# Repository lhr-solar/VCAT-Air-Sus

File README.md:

# Air-Suspension Boards

> **Project:** Longhorn Racing Solar - Hardware & Telemetry
> **Author:** Karthik Kurapati 

This repository contains the hardware design files for 4 sensors on the car: Suspension (Linear Potentiometers), Pitot, Temperature/Pressure, and RideHeight. 

## Table of Contents
1. [Telemetry CAN Overview](#CAN-overview)
2. [PSOM Boards](#psom-boards)
    - [Pitot Board](#1-pitot-board)
    - [Sus-RH (Suspension & Ride Height) Board](#2-sus-rh-board)
3. [Breakout Boards](#breakout-boards)
    - [Temperature Breakout](#3-temperature-breakout)
    - [Ride Height Breakout](#4-ride-height-breakout)

---

## Telemetry CAN Overview

P - Pitot Board
T - Temperature Breakout
L - Telemetry Leader
S - Sus-RH Board
RH - Sus-RH Board + Ride Height Breakout
W - Wheels Board

---

## PSOM Boards

These boards integrate a PSOM to collect data from sensors 

### 1. Pitot Board
**Function:** Measures the vehicle's true airspeed via a pitot sensor. Relays data sent by the temperature sensor to telemetry leader. 
**Sensors**: HSCDRRN010NDSA3

### 2. Sus-RH Board
**Function:** Measures linear potentiometer (suspension) travel on the car via ADC. Interfaces with ride height breakout. 
**Sensor:** LPPS-12

---

## Breakout Boards

Simple boards that use nano-fits to connect to the boards above to add functionality. Both breakouts use I2C to communicate over the distance. 

### 3. Temperature Breakout
**Function:** Provide valuable temperature, pressure, humidity, and air density information to improve estimate of airspeed. 
**Sensor:** BME280 

### 4. Ride Height Breakout (IR Board)
**Function:** Provides the distance from the bottom of the car to the road in multiple areas.
**Sensor** VL53L0X

---

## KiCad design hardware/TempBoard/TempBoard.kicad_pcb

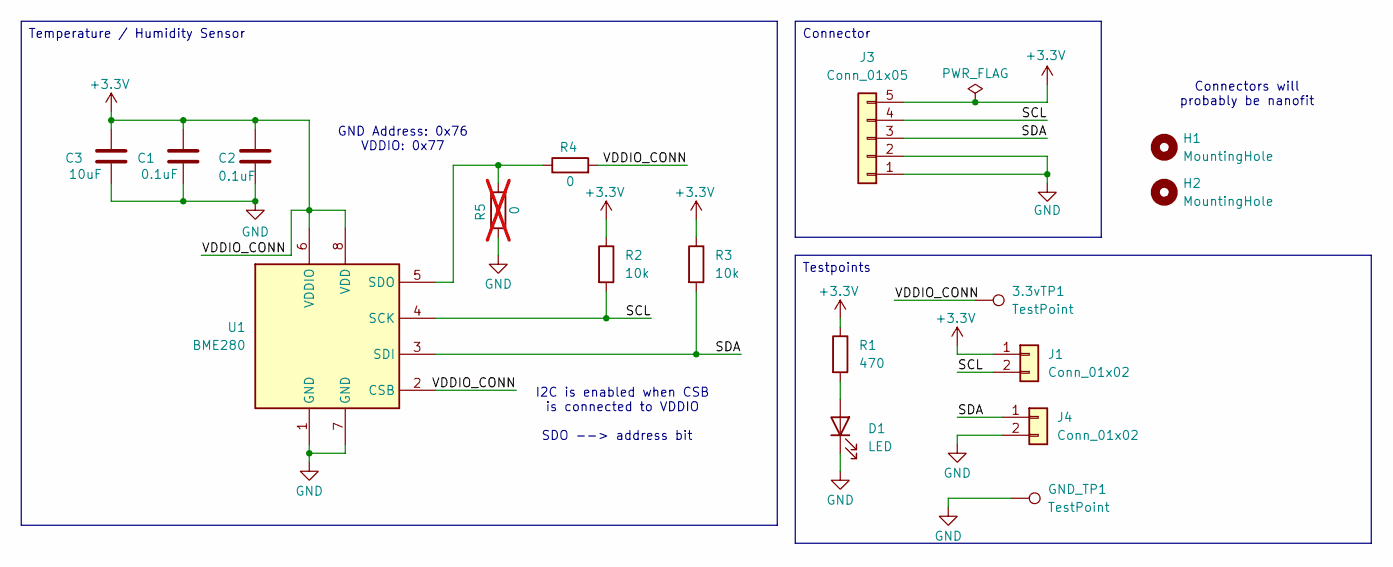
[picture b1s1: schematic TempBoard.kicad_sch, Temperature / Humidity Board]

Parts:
3.3vTP1: TestPoint; TestPoint_THTPad_1.0x1.0mm_Drill0.5mm
C1, C2: 0.1uF; C_0603_1608Metric_Pad1.08x0.95mm_HandSolder
C3: 10uF; C_0805_2012Metric_Pad1.18x1.45mm_HandSolder
D1: LED; LED_0603_1608Metric_Pad1.05x0.95mm_HandSolder
GND_TP1: TestPoint; TestPoint_THTPad_1.0x1.0mm_Drill0.5mm
H1, H2: MountingHole; MountingHole_3.2mm_M3
J1, J4: Conn_01x02; PinHeader_1x02_P2.54mm_Vertical
J3: Conn_01x05; Molex_Nano-Fit_105313-xx05_1x05_P2.50mm_Horizontal
R1: 470; R_0603_1608Metric_Pad0.98x0.95mm_HandSolder
R2, R3: 10k; R_0603_1608Metric_Pad0.98x0.95mm_HandSolder
R4: 0; R_0603_1608Metric_Pad0.98x0.95mm_HandSolder
R5: 0; R_0603_1608Metric_Pad0.98x0.95mm_HandSolder; not fitted
U1: BME280; Bosch_LGA-8_2.5x2.5mm_P0.65mm_ClockwisePinNumbering

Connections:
+3.3V: 3.3vTP1.1, C1.1, C2.1, C3.1, J1.1, J3.5, R1.1, R2.1, R3.1, R4.2, U1.2 (CSB), U1.6 (VDDIO), U1.8 (VDD)
/SCL: J1.2, J3.4, R2.2, U1.4 (SCK)
/SDA: J3.3, J4.1, R3.2, U1.3 (SDI)
GND: C1.2, C2.2, C3.2, D1.1 (K), GND_TP1.1, J3.1, J3.2, J4.2, R5.1, U1.1 (GND), U1.7 (GND)
unnamed: D1.2 (A), R1.2
unnamed: R4.1, R5.2, U1.5 (SDO)

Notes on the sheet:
Connectors will probably be nanofit
I2C is enabled when CSB is connected to VDDIO
GND Address: 0x76 VDDIO: 0x77
SDO --> address bit
Connector
Testpoints
Temperature / Humidity Sensor

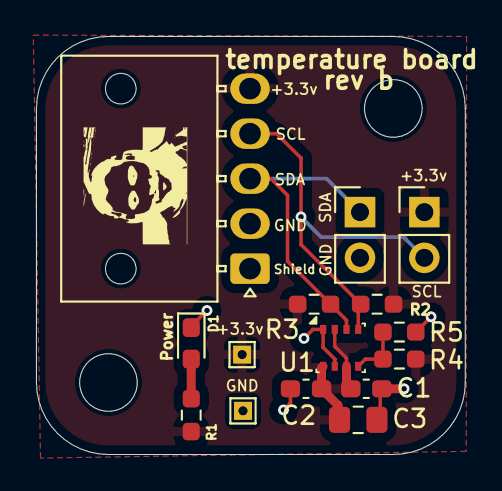
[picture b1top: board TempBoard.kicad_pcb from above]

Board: 2 copper layers, 23.8 x 23.2 mm, 17 parts (0 on the bottom side), 6 nets.

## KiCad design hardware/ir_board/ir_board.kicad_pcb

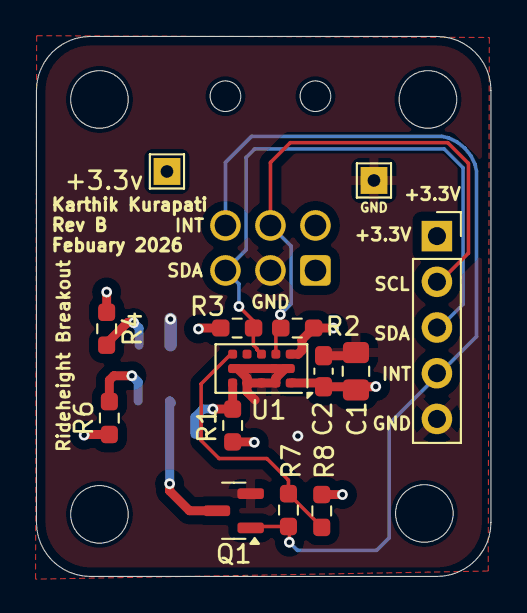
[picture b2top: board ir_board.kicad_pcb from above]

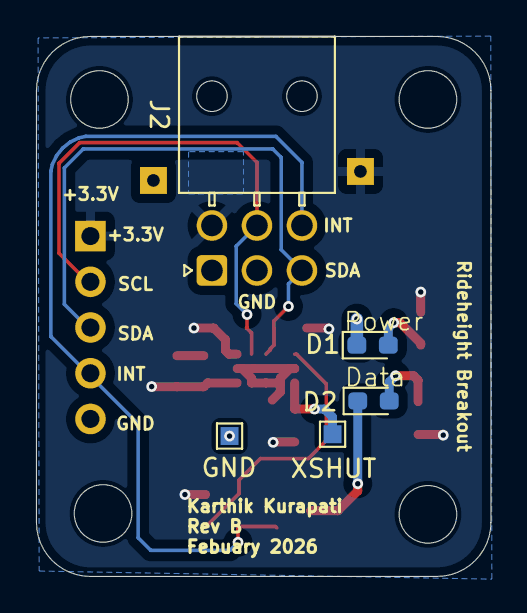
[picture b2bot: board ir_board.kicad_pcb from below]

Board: 2 copper layers, 25.2 x 30.0 mm, 23 parts (5 on the bottom side), 10 nets.

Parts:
+3.3v: TestPoint; TestPoint_THTPad_1.5x1.5mm_Drill0.7mm
C1: 4.7uf; C_0805_2012Metric_Pad1.18x1.45mm_HandSolder
C2: 0.1uf; C_0603_1608Metric_Pad1.08x0.95mm_HandSolder
D1, D2: LED; LED_0603_1608Metric_Pad1.05x0.95mm_HandSolder
GND: TestPoint; TestPoint_THTPad_1.5x1.5mm_Drill0.7mm
GND#2: TestPoint; TestPoint_Pad_1.0x1.0mm
H1, H2, H3, H4: MountingHole; MountingHole_3.2mm_M3
J1: Conn_01x05; PinSocket_1x05_P2.54mm_Vertical
J2: Conn_01x06; Molex_Nano-Fit_105314-xx06_2x03_P2.50mm_Horizontal
Q1: IRLML0030; SOT-23
R1: 10k; R_0603_1608Metric_Pad0.98x0.95mm_HandSolder
R2, R3, R8: 4.7k; R_0603_1608Metric_Pad0.98x0.95mm_HandSolder
R4, R6: 1k; R_0603_1608Metric_Pad0.98x0.95mm_HandSolder
R7: 0; R_0603_1608Metric_Pad0.98x0.95mm_HandSolder
U1: VL53L0CXV0DH1; ST_VL53L1x
XSHUT: TestPoint; TestPoint_Pad_1.0x1.0mm

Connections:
+3.3V: +3.3v.1, C1.1, C2.1, J1.1, J2.4, R1.1, R2.1, R3.1, R4.1, R6.1, R8.1, U1.1 (AVDDVCSEL), U1.11 (AVDD)
/GPIO1: J1.4, J2.6, Q1.1 (G), R7.1
/SCL: J1.2, J2.5, R2.2, U1.10 (SCL)
/SDA: J1.3, J2.3, R3.2, U1.9 (SDA)
/XSHUT: R1.2, U1.5 (XSHUT), XSHUT.1
GND: C1.2, C2.2, D1.1 (K), GND.1, GND#2.1, J1.5, J2.2, Q1.2 (S), U1.2 (AVSSVCSEL), U1.3 (GND), U1.4 (GND), U1.6 (GND), U1.12 (GND)
unnamed: D1.2 (A), R4.2
unnamed: D2.2 (A), R6.2
unnamed: D2.1 (K), Q1.3 (D)
unnamed: R7.2, R8.2, U1.7 (GPIO1)

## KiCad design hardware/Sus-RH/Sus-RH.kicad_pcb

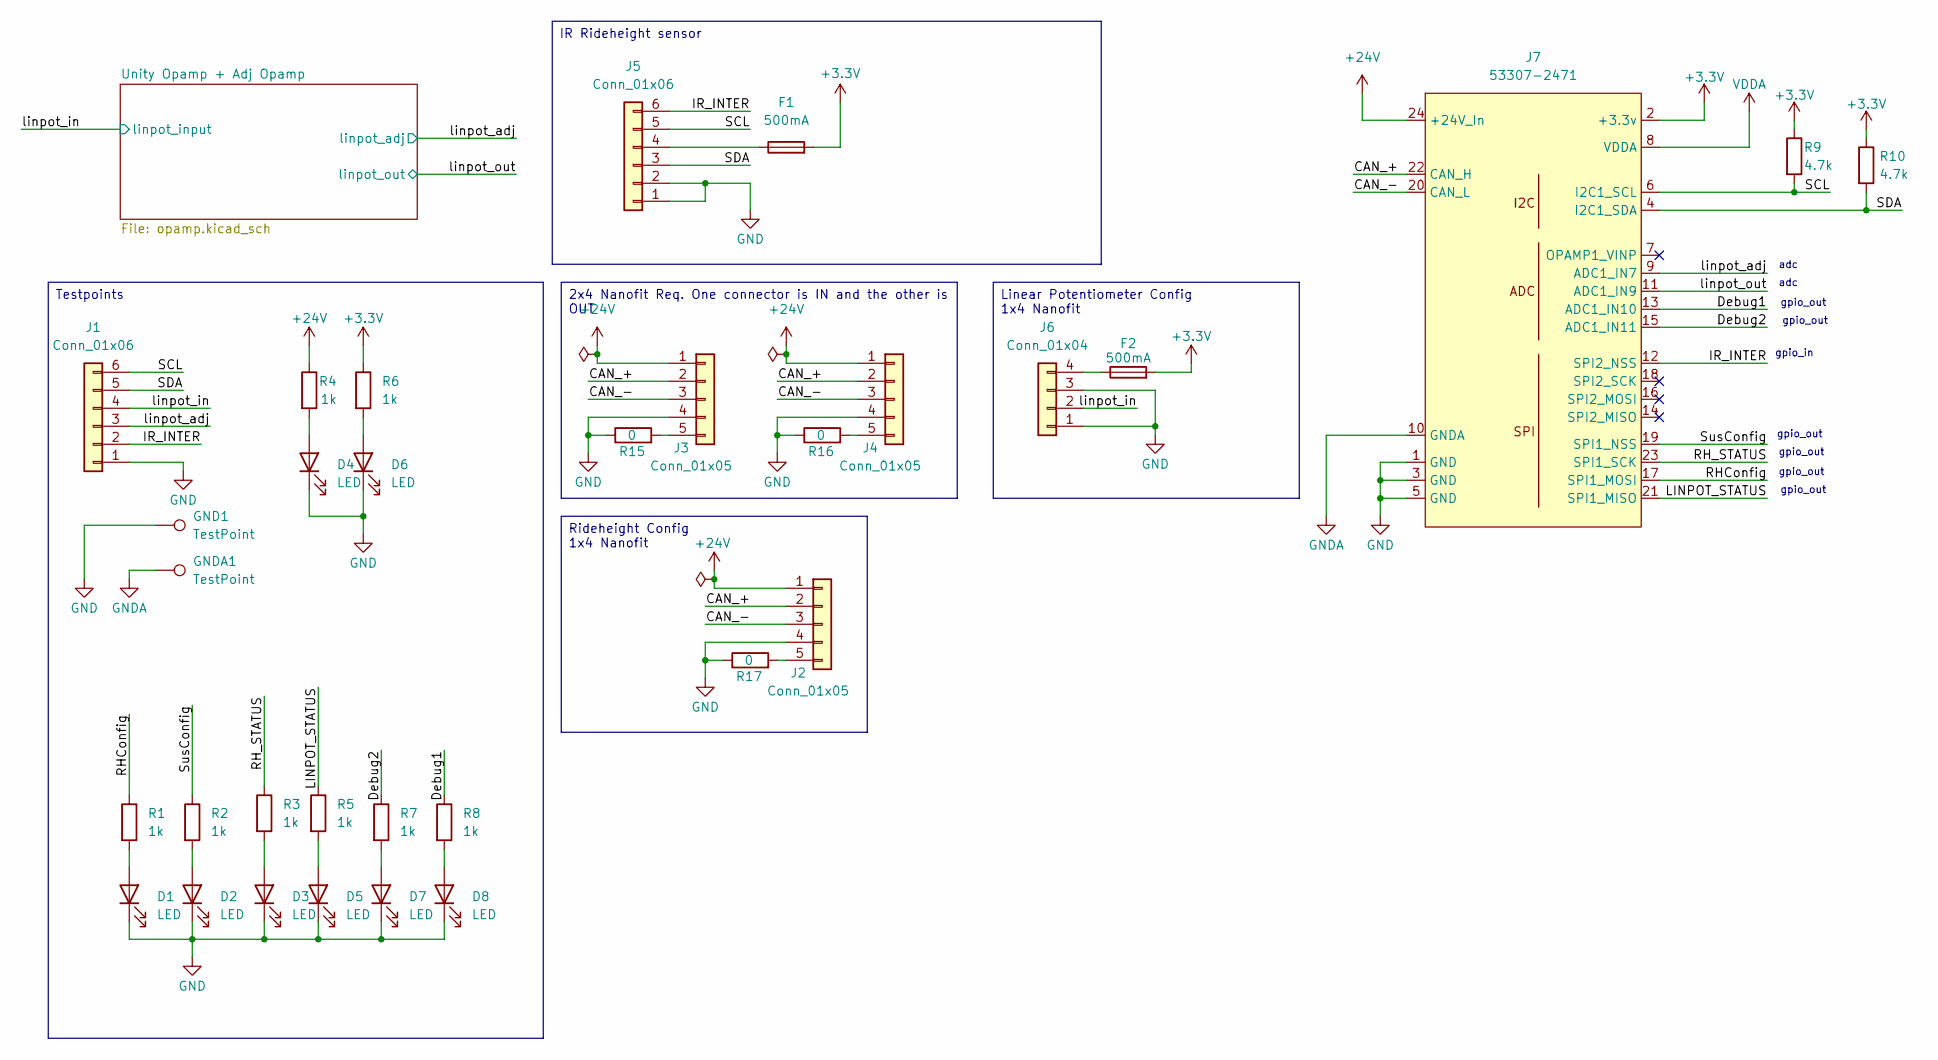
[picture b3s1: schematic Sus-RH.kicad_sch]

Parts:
D1, D2, D3, D4, D5, D6, D7, D8: LED; LED_0603_1608Metric_Pad1.05x0.95mm_HandSolder
F1, F2: 500mA; Fuse_0603_1608Metric_Pad1.05x0.95mm_HandSolder
GND1: TestPoint; TestPoint_THTPad_2.5x2.5mm_Drill1.2mm
GNDA1: TestPoint; TestPoint_THTPad_1.5x1.5mm_Drill0.7mm
J1: Conn_01x06; PinHeader_1x06_P2.54mm_Vertical
J2, J3, J4: Conn_01x05; Molex_Nano-Fit_105313-xx05_1x05_P2.50mm_Horizontal
J5: Conn_01x06; Molex_Nano-Fit_105314-xx06_2x03_P2.50mm_Horizontal
J6: Conn_01x04; Molex_Nano-Fit_105313-xx04_1x04_P2.50mm_Horizontal
J7: 53307-2471; PeripheralSOM
R1, R2, R3, R4, R5, R6, R7, R8: 1k; R_0603_1608Metric_Pad0.98x0.95mm_HandSolder
R9, R10: 4.7k; R_0603_1608Metric_Pad0.98x0.95mm_HandSolder
R15, R16, R17: 0; R_0603_1608Metric_Pad0.98x0.95mm_HandSolder

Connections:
+3.3V: F1.2, F2.2, J7.2 (+3.3v), R6.1, R9.1, R10.1
+24V: J2.1, J3.1, J4.1, J7.24 (+24V_In), R4.1
/CAN_+: J2.2, J3.2, J4.2, J7.22 (CAN_H)
/CAN_-: J2.3, J3.3, J4.3, J7.20 (CAN_L)
/Debug1: J7.13 (ADC1_IN10), R8.1
/Debug2: J7.15 (ADC1_IN11), R7.1
/IR_INTER: J1.2, J5.6, J7.12 (SPI2_NSS)
/LINPOT_STATUS: J7.21 (SPI1_MISO), R5.1
/RHConfig: J7.17 (SPI1_MOSI), R1.1
/RH_STATUS: J7.23 (SPI1_SCK), R3.1
/SCL: J1.6, J5.5, J7.6 (I2C1_SCL), R9.2
/SDA: J1.5, J5.3, J7.4 (I2C1_SDA), R10.2
/SusConfig: J7.19 (SPI1_NSS), R2.1
/linpot_adj: J1.3, J7.9 (ADC1_IN7); also elsewhere on the board
/linpot_in: J1.4, J6.2; also elsewhere on the board
/linpot_out: J7.11 (ADC1_IN9); also elsewhere on the board
GND: D1.1 (K), D2.1 (K), D3.1 (K), D4.1 (K), D5.1 (K), D6.1 (K), D7.1 (K), D8.1 (K), GND1.1, J1.1, J2.4, J3.4, J4.4, J5.1, J5.2, J6.1, J6.3, J7.1 (GND), J7.3 (GND), J7.5 (GND), R15.1, R16.1, R17.1; also elsewhere on the board
GNDA: GNDA1.1, J7.10 (GNDA); also elsewhere on the board
unnamed: D1.2 (A), R1.2
unnamed: D2.2 (A), R2.2
unnamed: D3.2 (A), R3.2
unnamed: D4.2 (A), R4.2
unnamed: D5.2 (A), R5.2
unnamed: D6.2 (A), R6.2
unnamed: D7.2 (A), R7.2
unnamed: D8.2 (A), R8.2
unnamed: J2.5, R17.2
unnamed: J3.5, R15.2
unnamed: J4.5, R16.2
unnamed: F1.1, J5.4
unnamed: F2.1, J6.4
VDDA: J7.8 (VDDA); also elsewhere on the board

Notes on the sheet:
gpio_in
adc
gpio_out
Rideheight Config 1x4 Nanofit
IR Rideheight sensor
2x4 Nanofit Req. One connector is IN and the other is OUT
Testpoints
Linear Potentiometer Config 1x4 Nanofit

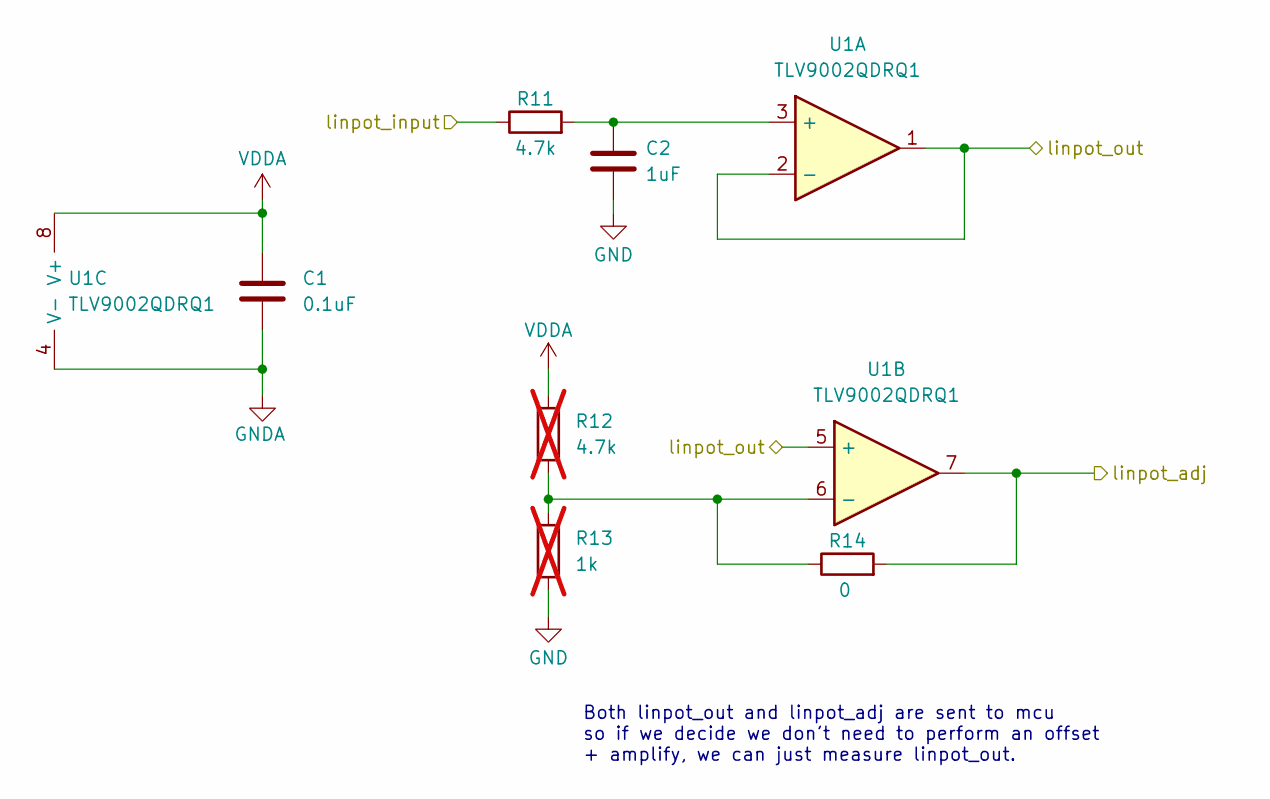
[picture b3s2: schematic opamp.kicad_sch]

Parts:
C1: 0.1uF; C_0603_1608Metric_Pad1.08x0.95mm_HandSolder
C2: 1uF; C_0603_1608Metric_Pad1.08x0.95mm_HandSolder
R11: 4.7k; R_0603_1608Metric_Pad0.98x0.95mm_HandSolder
R12: 4.7k; R_0603_1608Metric_Pad0.98x0.95mm_HandSolder; not fitted
R13: 1k; R_0603_1608Metric_Pad0.98x0.95mm_HandSolder; not fitted
R14: 0; R_0603_1608Metric_Pad0.98x0.95mm_HandSolder
U1: TLV9002QDRQ1; SOIC8_D_TEX; Mouser P/N 595-TLV9002QDRQ1

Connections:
/linpot_adj: R14.2, U1.7; also elsewhere on the board
/linpot_in: R11.1; also elsewhere on the board
/linpot_out: U1.1, U1.2 (-), U1.5 (+); also elsewhere on the board
GND: C2.2, R13.2; also elsewhere on the board
GNDA: C1.2, U1.4 (V-); also elsewhere on the board
unnamed: C2.1, R11.2, U1.3 (+)
unnamed: R12.2, R13.1, R14.1, U1.6 (-)
VDDA: C1.1, R12.1, U1.8 (V+); also elsewhere on the board

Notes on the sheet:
Both linpot_out and linpot_adj are sent to mcu so if we decide we don't need to perform an offset + amplify, we can just measure linpot_out.

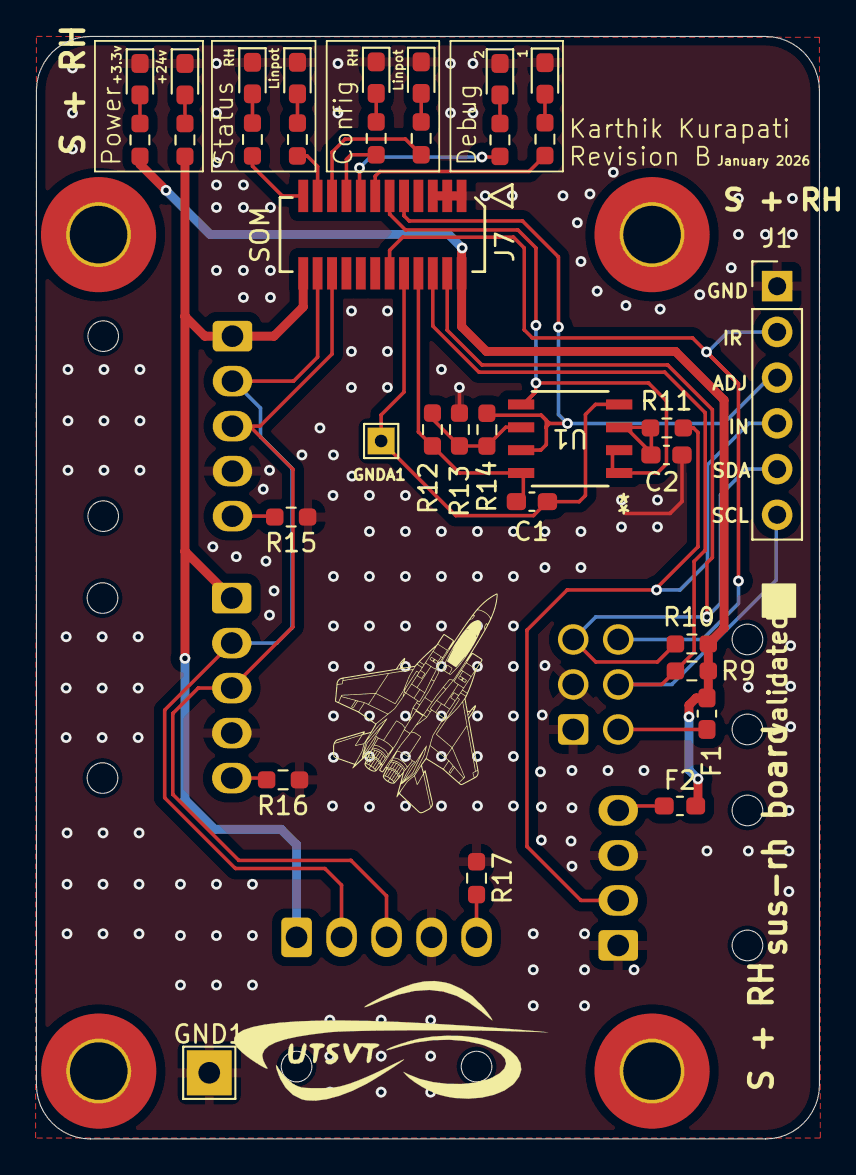
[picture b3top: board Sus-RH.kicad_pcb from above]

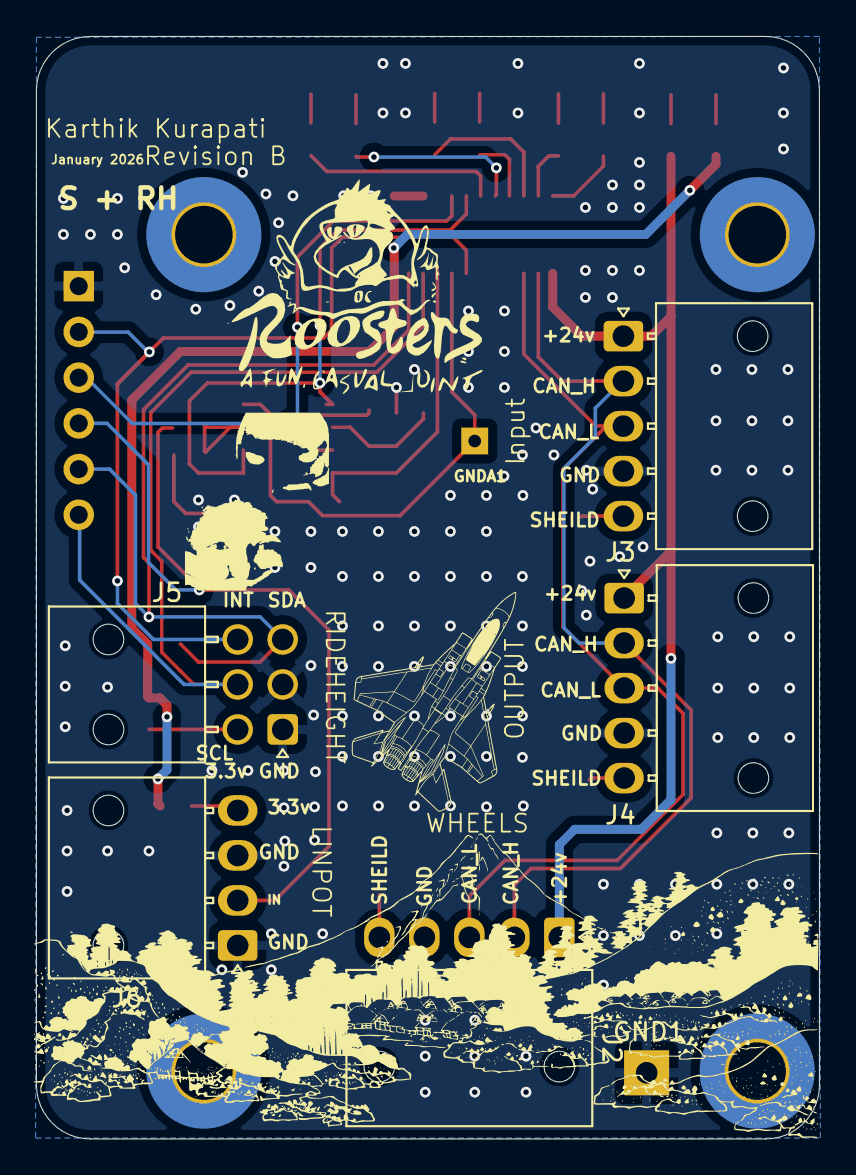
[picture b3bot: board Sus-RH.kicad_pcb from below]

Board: 2 copper layers, 43.5 x 61.2 mm, 39 parts (5 on the bottom side), 34 nets.

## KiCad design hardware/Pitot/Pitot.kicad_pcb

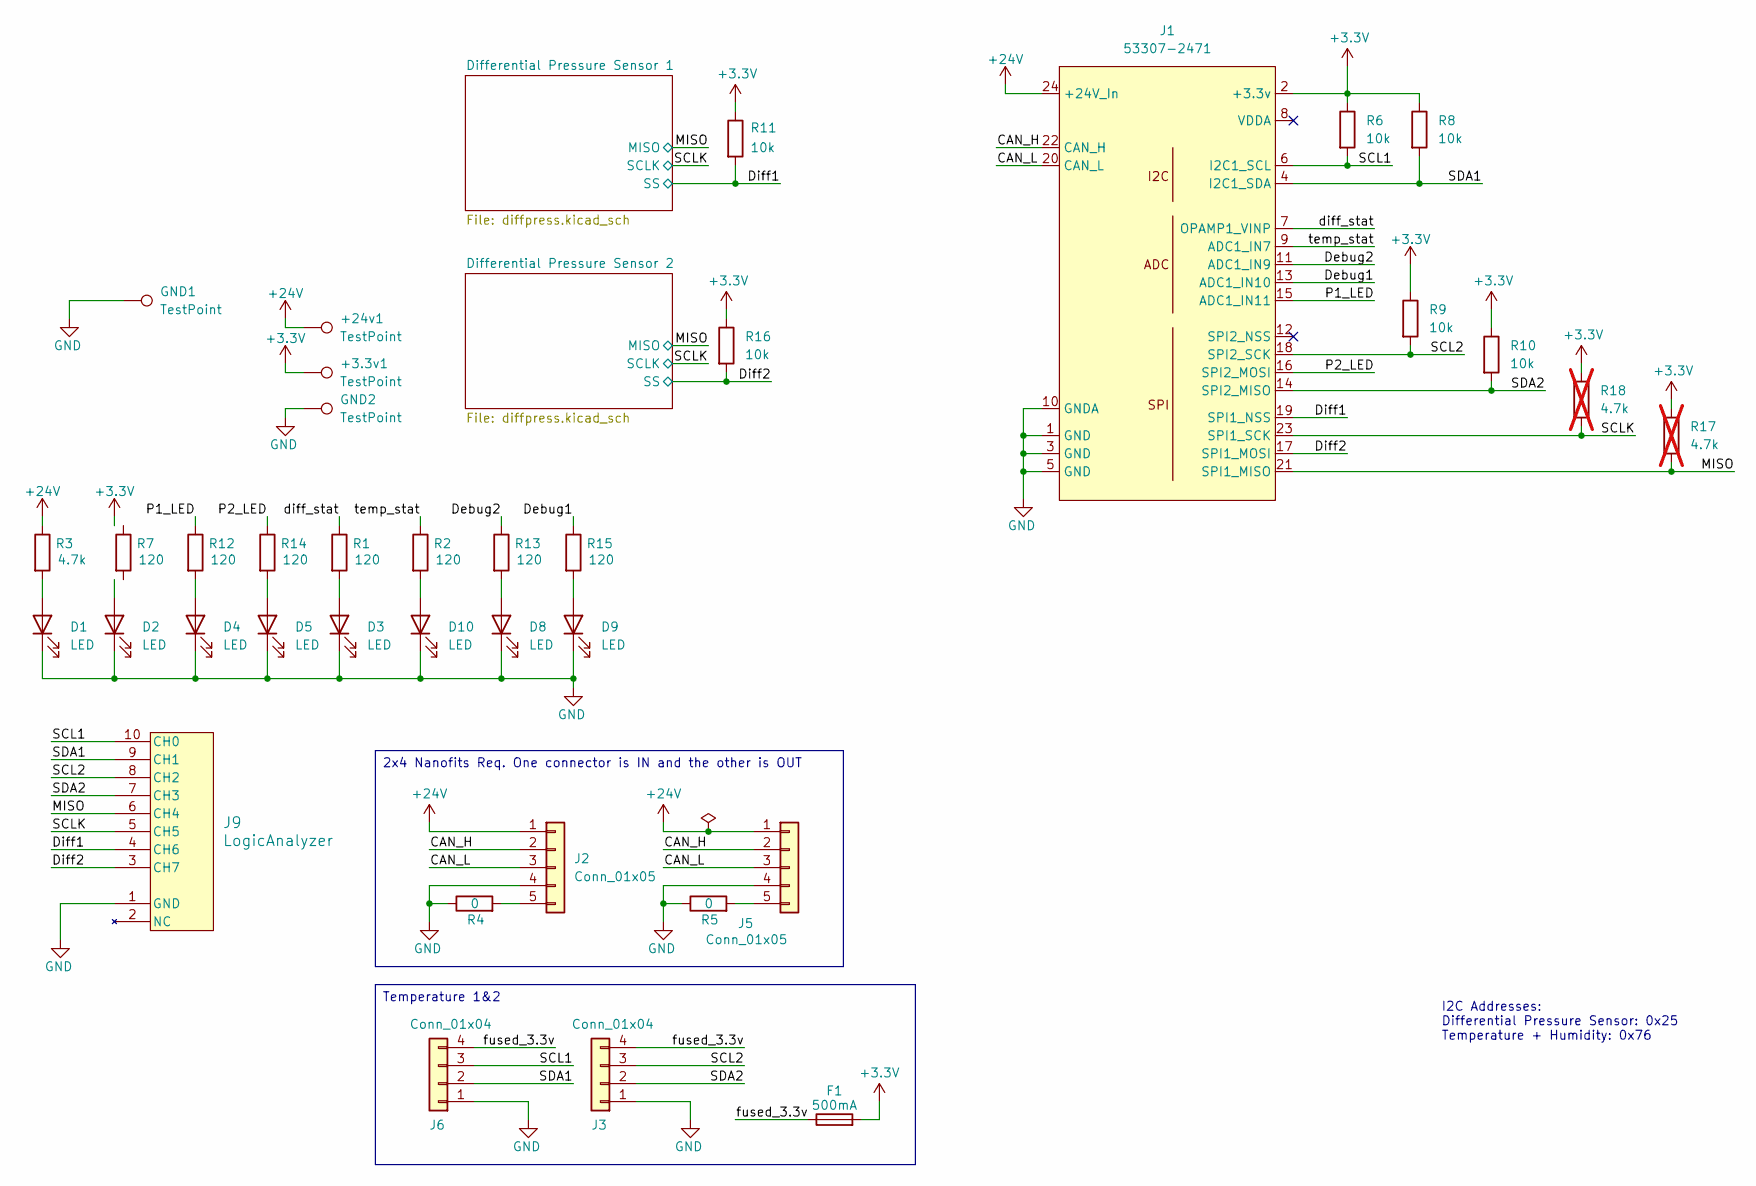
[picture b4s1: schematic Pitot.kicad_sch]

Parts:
+3.3v1, +24v1: TestPoint; TestPoint_THTPad_2.0x2.0mm_Drill1.0mm
D1, D5, D8, D10: LED; LED_0603_1608Metric_Pad1.05x0.95mm_HandSolder; JLC P/N C7371904
D2, D3, D4, D9: LED; LED_0603_1608Metric_Pad1.05x0.95mm_HandSolder; JLC P/N C84263
F1: 500mA; Fuse_0603_1608Metric_Pad1.05x0.95mm_HandSolder
GND1, GND2: TestPoint; TestPoint_THTPad_2.0x2.0mm_Drill1.0mm
J1: 53307-2471; PeripheralSOM
J2, J5: Conn_01x05; Molex_Nano-Fit_105313-xx05_1x05_P2.50mm_Horizontal
J3, J6: Conn_01x04; Molex_Nano-Fit_105313-xx04_1x04_P2.50mm_Horizontal
J9: LogicAnalyzer; CONN_SFH11-xxxC-D05-ST-XX_SUL; Digikey P/N S9194-ND
R1, R2, R7, R12, R13, R14, R15: 120; R_0603_1608Metric_Pad0.98x0.95mm_HandSolder
R3: 4.7k; R_0603_1608Metric_Pad0.98x0.95mm_HandSolder
R4, R5: 0; R_0603_1608Metric_Pad0.98x0.95mm_HandSolder
R6, R8, R9, R10, R11, R16: 10k; R_0603_1608Metric_Pad0.98x0.95mm_HandSolder
R17, R18: 4.7k; R_0603_1608Metric_Pad0.98x0.95mm_HandSolder; not fitted

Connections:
+3.3V: +3.3v1.1, F1.2, J1.2 (+3.3v), R6.1, R7.1, R8.1, R9.1, R10.1, R11.1, R16.1, R17.1, R18.1; also elsewhere on the board
+24V: +24v1.1, J1.24 (+24V_In), J2.1, J5.1, R3.1
/CAN_H: J1.22 (CAN_H), J2.2, J5.2
/CAN_L: J1.20 (CAN_L), J2.3, J5.3
/Debug1: J1.13 (ADC1_IN10), R15.1
/Debug2: J1.11 (ADC1_IN9), R13.1
/Diff1: J1.19 (SPI1_NSS), J9.4 (CH6), R11.2; also elsewhere on the board
/Diff2: J1.17 (SPI1_MOSI), J9.3 (CH7), R16.2; also elsewhere on the board
/MISO: J1.21 (SPI1_MISO), J9.6 (CH4), R17.2; also elsewhere on the board
/P1_LED: J1.15 (ADC1_IN11), R12.1
/P2_LED: J1.16 (SPI2_MOSI), R14.1
/SCL1: J1.6 (I2C1_SCL), J6.3, J9.10 (CH0), R6.2
/SCL2: J1.18 (SPI2_SCK), J3.3, J9.8 (CH2), R9.2
/SCLK: J1.23 (SPI1_SCK), J9.5 (CH5), R18.2; also elsewhere on the board
/SDA1: J1.4 (I2C1_SDA), J6.2, J9.9 (CH1), R8.2
/SDA2: J1.14 (SPI2_MISO), J3.2, J9.7 (CH3), R10.2
/diff_stat: J1.7 (OPAMP1_VINP), R1.1
/fused_3.3v: F1.1, J3.4, J6.4
/temp_stat: J1.9 (ADC1_IN7), R2.1
GND: D1.1 (K), D2.1 (K), D3.1 (K), D4.1 (K), D5.1 (K), D8.1 (K), D9.1 (K), D10.1 (K), GND1.1, GND2.1, J1.1 (GND), J1.3 (GND), J1.5 (GND), J1.10 (GNDA), J2.4, J3.1, J5.4, J6.1, J9.1 (GND), R4.1, R5.1; also elsewhere on the board
unnamed: D1.2 (A), R3.2
unnamed: D2.2 (A), R7.2
unnamed: D3.2 (A), R1.2
unnamed: D4.2 (A), R12.2
unnamed: D5.2 (A), R14.2
unnamed: D8.2 (A), R13.2
unnamed: D9.2 (A), R15.2
unnamed: D10.2 (A), R2.2
unnamed: J2.5, R4.2
unnamed: J5.5, R5.2

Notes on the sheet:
I2C Addresses: Differential Pressure Sensor: 0x25 Temperature + Humidity: 0x76
Temperature 1&2
2x4 Nanofits Req. One connector is IN and the other is OUT

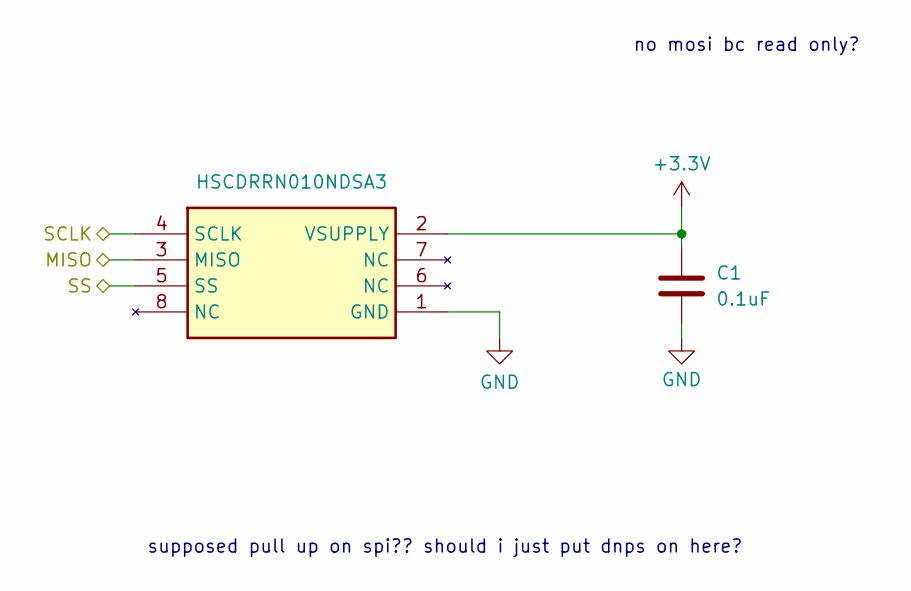
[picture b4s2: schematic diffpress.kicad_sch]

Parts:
C1: 0.1uF; C_0603_1608Metric_Pad1.08x0.95mm_HandSolder
IC1: HSCDRRN010NDSA3

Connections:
+3.3V: C1.1, IC1.2 (VSUPPLY); also elsewhere on the board
/Diff1: IC1.5 (SS); also elsewhere on the board
/MISO: IC1.3 (MISO); also elsewhere on the board
/SCLK: IC1.4 (SCLK); also elsewhere on the board
GND: C1.2, IC1.1 (GND); also elsewhere on the board

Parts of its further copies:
C2: 0.1uF; C_0603_1608Metric_Pad1.08x0.95mm_HandSolder
IC2: HSCDRRN010NDSA3

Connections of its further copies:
+3.3V: C2.1, IC2.2 (VSUPPLY); also elsewhere on the board
/Diff2: IC2.5 (SS); also elsewhere on the board
/MISO: IC2.3 (MISO); also elsewhere on the board
/SCLK: IC2.4 (SCLK); also elsewhere on the board
GND: C2.2, IC2.1 (GND); also elsewhere on the board

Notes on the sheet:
supposed pull up on spi?? should i just put dnps on here?
no mosi bc read only?

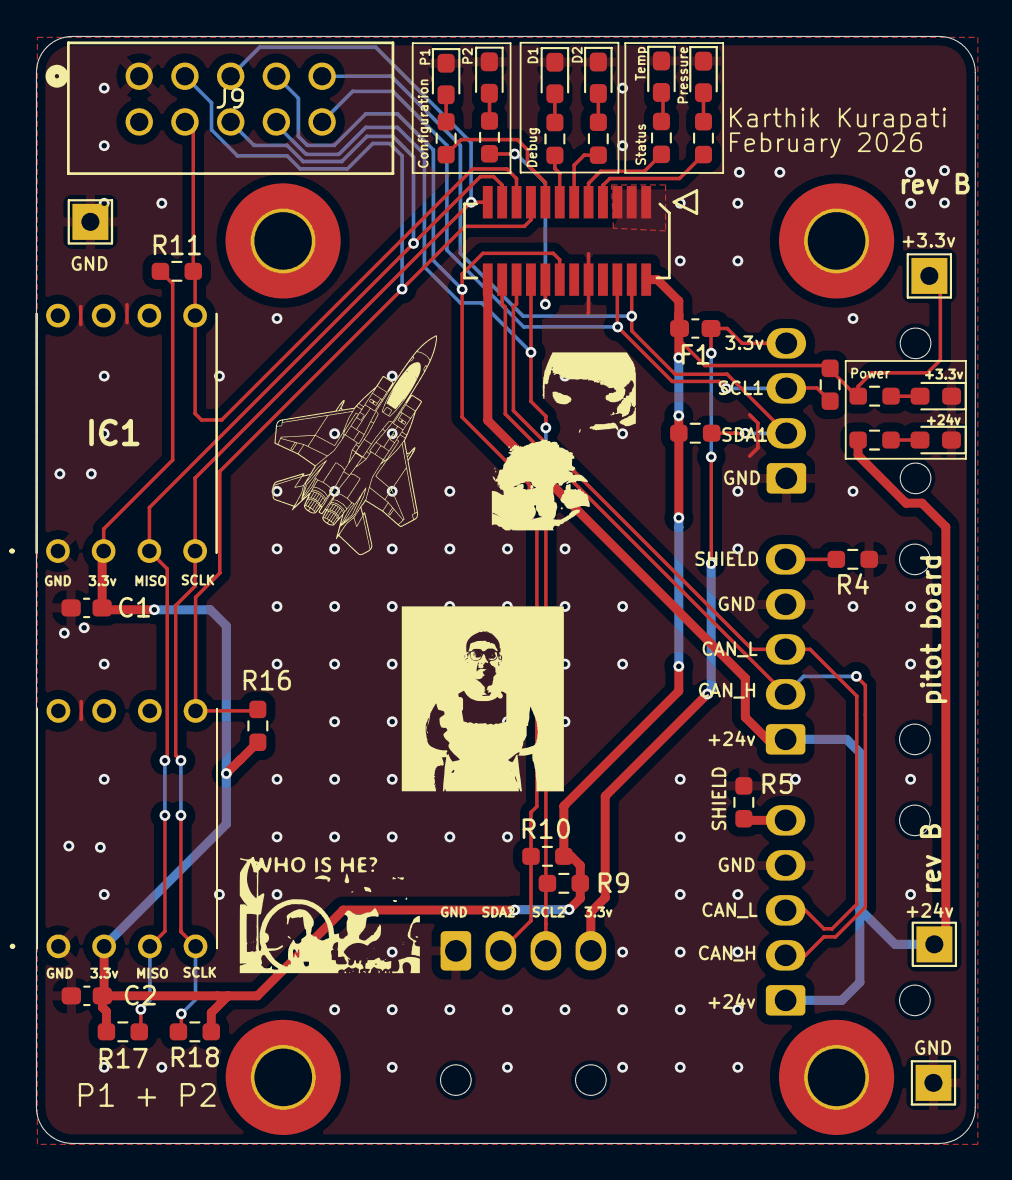
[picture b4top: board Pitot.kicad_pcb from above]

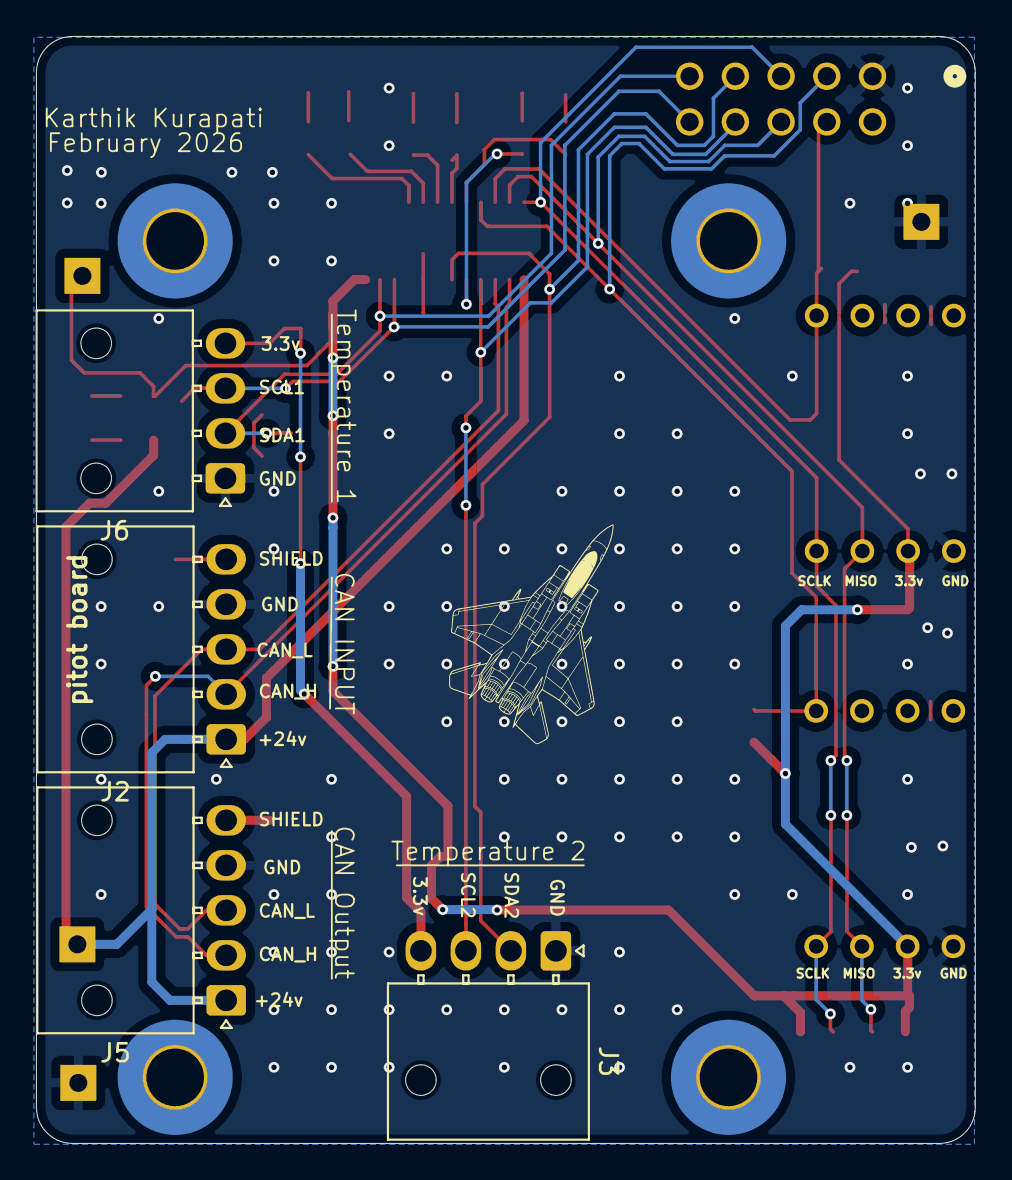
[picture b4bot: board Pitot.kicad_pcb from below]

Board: 2 copper layers, 52.2 x 61.5 mm, 41 parts (4 on the bottom side), 30 nets.

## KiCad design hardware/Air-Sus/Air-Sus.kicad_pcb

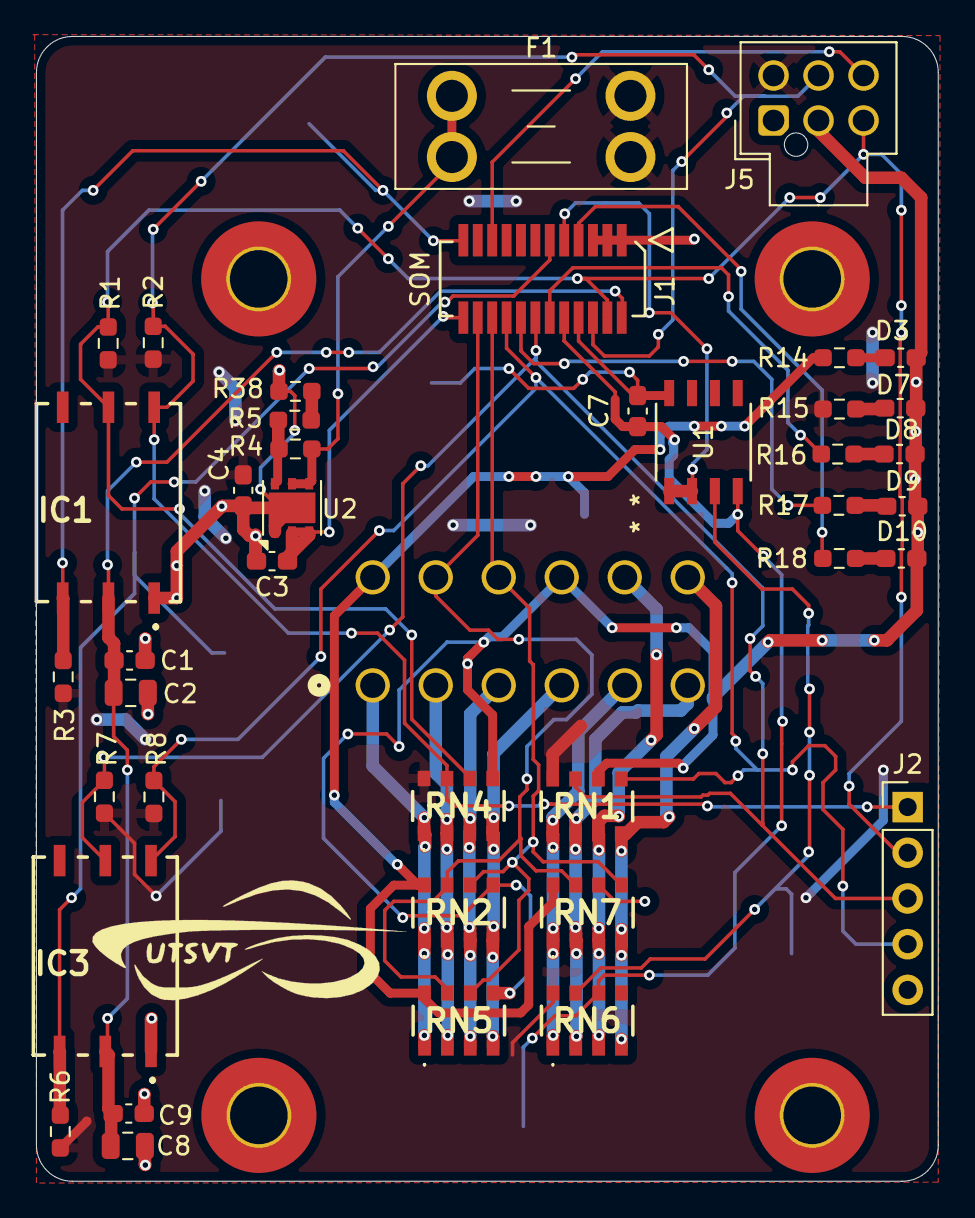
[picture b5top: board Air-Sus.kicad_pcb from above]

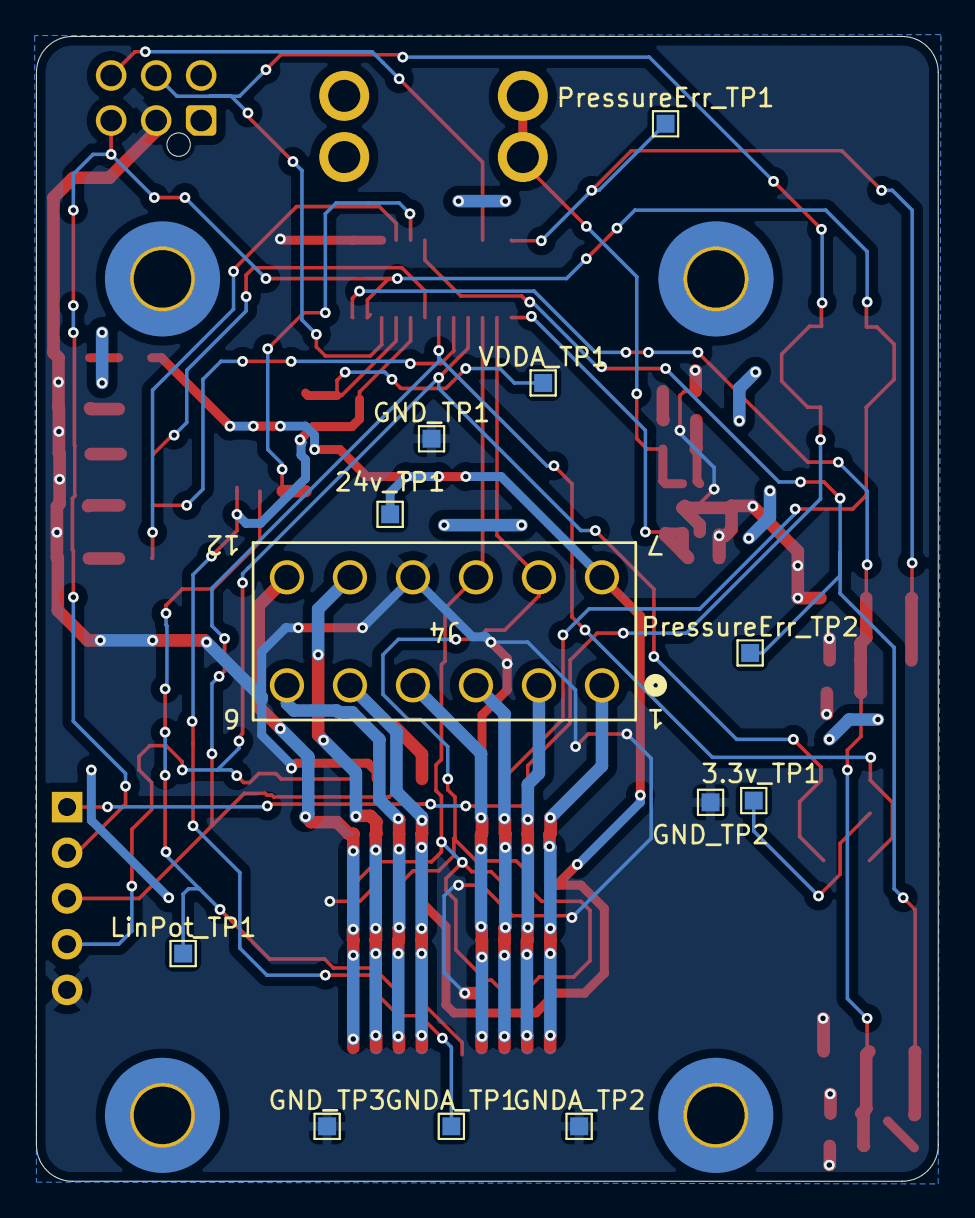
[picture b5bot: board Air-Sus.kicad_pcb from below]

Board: 2 copper layers, 50.1 x 63.6 mm, 52 parts (12 on the bottom side), 37 nets.

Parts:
3.3v_TP1, 24v_TP1: TestPoint; TestPoint_Pad_1.0x1.0mm
C1, C7, C9: 0.1uF; C_0603_1608Metric_Pad1.08x0.95mm_HandSolder
C2, C8: 10uf; C_0805_2012Metric
C3, C4: 1uF; C_0603_1608Metric_Pad1.08x0.95mm_HandSolder
D3, D7, D8, D9, D10: LED; C_0603_1608Metric_Pad1.08x0.95mm_HandSolder
F1: 500mA; Fuseholder_Blade_Mini_Keystone_3568
GNDA_TP1, GNDA_TP2: TestPoint; TestPoint_Pad_1.0x1.0mm
GND_TP1, GND_TP2, GND_TP3: TestPoint; TestPoint_Pad_1.0x1.0mm
IC1, IC3: ABPMRRV060MG2A3
J1: 53307-2471; PeripheralSOM
J2: Conn_01x05; PinHeader_1x05_P2.54mm_Vertical
J4: MX150_02x06_Vertical
J5: Conn_01x06; Molex_Nano-Fit_105310-xx06_2x03_P2.50mm_Vertical
LinPot_TP1: TestPoint; TestPoint_Pad_1.0x1.0mm
PressureErr_TP1, PressureErr_TP2: TestPoint; TestPoint_Pad_1.0x1.0mm
R1, R2, R3, R6, R7, R8: 4.7k; R_0603_1608Metric_Pad0.98x0.95mm_HandSolder
R4: 10k; R_0603_1608Metric_Pad0.98x0.95mm_HandSolder
R5: 15k; R_0603_1608Metric_Pad0.98x0.95mm_HandSolder
R14, R15, R16, R17, R18: 1k; R_0603_1608Metric_Pad0.98x0.95mm_HandSolder
R38: 2.49k; R_0603_1608Metric_Pad0.98x0.95mm_HandSolder
RN1, RN2, RN4, RN5, RN6, RN7: YC324-JK-070RL; YC324JK07220RL
U1: Opamp_Dual; SOIC8_D_TEX
U2: LDO40LPURY; DFN-6-1EP_3x3mm_P0.95mm_EP1.7x2.6mm
VDDA_TP1: TestPoint; TestPoint_Pad_1.0x1.0mm

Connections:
+3.3V: 3.3v_TP1.1, C4.1, F1.2, J5.4, R1.1, R2.1, R3.1, R6.1, R7.1, R8.1, R15.1, RN1.8, RN4.8, RN6.8
+3.3V MCU: C1.1, C2.1, C8.1, C9.1, IC1.2 (VSUPPLY), IC3.2 (VSUPPLY), J1.2 (+3.3v)
+24V: 24v_TP1.1, J4.7 (GND), R14.1, RN2.8, RN5.8, RN7.8
/24v_out: C3.1, J1.24 (+24V_In), U2.2 (EN), U2.3 (Vin)
/CAN_H: J1.22 (CAN_H), J4.8 (CANH_OUT), RN2.7, RN5.7, RN7.7
/CAN_L: J1.20 (CAN_L), J4.9 (CANL_OUT), RN2.6, RN5.6, RN7.5
/IR_INTER: J1.19 (SPI1_NSS), J5.6
/SCL: IC1.6 (SCL), J1.6 (I2C1_SCL), J2.1, J5.5, R2.2, RN4.7
/SCL2: IC3.6 (SCL), J1.18 (SPI2_SCK), J2.4, R8.2, RN1.5
/SDA: IC1.5 (SDA), J1.4 (I2C1_SDA), J2.2, J5.3, R1.2, RN4.6
/SDA2: IC3.5 (SDA), J1.14 (SPI2_MISO), J2.3, R7.2, RN1.7
/Temp_status: J1.7 (OPAMP1_VINP), R18.1
/diff_status: J1.12 (SPI2_NSS), R16.1
/ir_status: J1.16 (SPI2_MOSI), R17.1
/linpot_norm: J1.9 (ADC1_IN7), U1.1, U1.2 (-)
/mx150Connector/Gen_1: J4.1 (+24V), RN2.1, RN4.1, RN5.1
/mx150Connector/Gen_2: J4.2 (CANH_IN), RN2.2, RN4.2, RN5.2
/mx150Connector/Gen_3: J4.3 (CANL_IN), RN2.3, RN4.3, RN5.3
/mx150Connector/Gen_4: J4.4 (PWR_OUT*), RN2.4, RN4.4, RN5.4
/mx150Connector/Gen_5: J4.5, RN1.1, RN6.1, RN7.1
/mx150Connector/Gen_6: J4.6, RN1.2, RN6.2, RN7.2
/mx150Connector/Gen_7: J4.11, RN1.3, RN6.3, RN7.3
/mx150Connector/Gen_8: J4.12, RN1.4, RN6.4, RN7.4
/pressure_err1: IC1.3 (INT), J1.23 (SPI1_SCK), PressureErr_TP1.1, R3.2
/pressure_err2: IC3.3 (INT), J1.11 (ADC1_IN9), PressureErr_TP2.1, R6.2
GND: C1.2, C2.2, C3.2, C4.2, C8.2, C9.2, D3.1 (K), D7.1 (K), D8.1 (K), D9.1 (K), D10.1 (K), GNDA_TP2.1, GND_TP1.1, GND_TP2.1, GND_TP3.1, IC1.1 (GND), IC3.1 (GND), J1.1 (GND), J1.3 (GND), J1.5 (GND), J2.5, J4.10 (GND_OUT*), J5.2, R38.2, RN1.6, RN2.5, RN4.5, RN5.5, RN7.6, U2.1 (GND), U2.7 (GND)
GNDA: C7.2, GNDA_TP1.1, J1.10 (GNDA), RN6.6, U1.4 (V-)
unnamed: D3.2 (A), R14.2
unnamed: D7.2 (A), R15.2
unnamed: D8.2 (A), R16.2
unnamed: D9.2 (A), R17.2
unnamed: D10.2 (A), R18.2
unnamed: R5.2, R38.1
unnamed: R4.2, R5.1, U2.6 (ADJ)
unnamed: F1.1, R4.1, U2.4 (Vout), U2.5 (Vsense)
VDDA: C7.1, J1.8 (VDDA), U1.8 (V+), VDDA_TP1.1
linpot_out: LinPot_TP1.1, RN6.7, U1.3 (+)
